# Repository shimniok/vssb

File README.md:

A Vehicle Speed Sensor Buffer (VSSB) for GM Throttle Body Injection (TBI) ECM on my 86 Jeep
Grand Wagoneer.

The Jeep GW uses a VSS for cruise control that outputs 8-pulse (8000 pulses/mile) sine wave
This circuit and firmware convert the OEM VSS signal to a 2-pulse square wave 5V signal
compatible with the GM TBI ECM ('7747) that I'm using.

It also outputs a 4-pulse signal which would be used (I think) by electronic GM speedos. 
The GW speedo, of course, is mechanical.

So what's the advantage of having a working speed sensor? At least a couple of TBI features
are enabled. The ECM is able to distinguish between idle mode (vehicle speed < 4mph) and
throttle-off coasting.  Additionally, Deceleration Fuel Cut-Off (DCFO) mode is enabled in
part based on speed.  And, if enabled, lean highway cruise is based on speed as well.

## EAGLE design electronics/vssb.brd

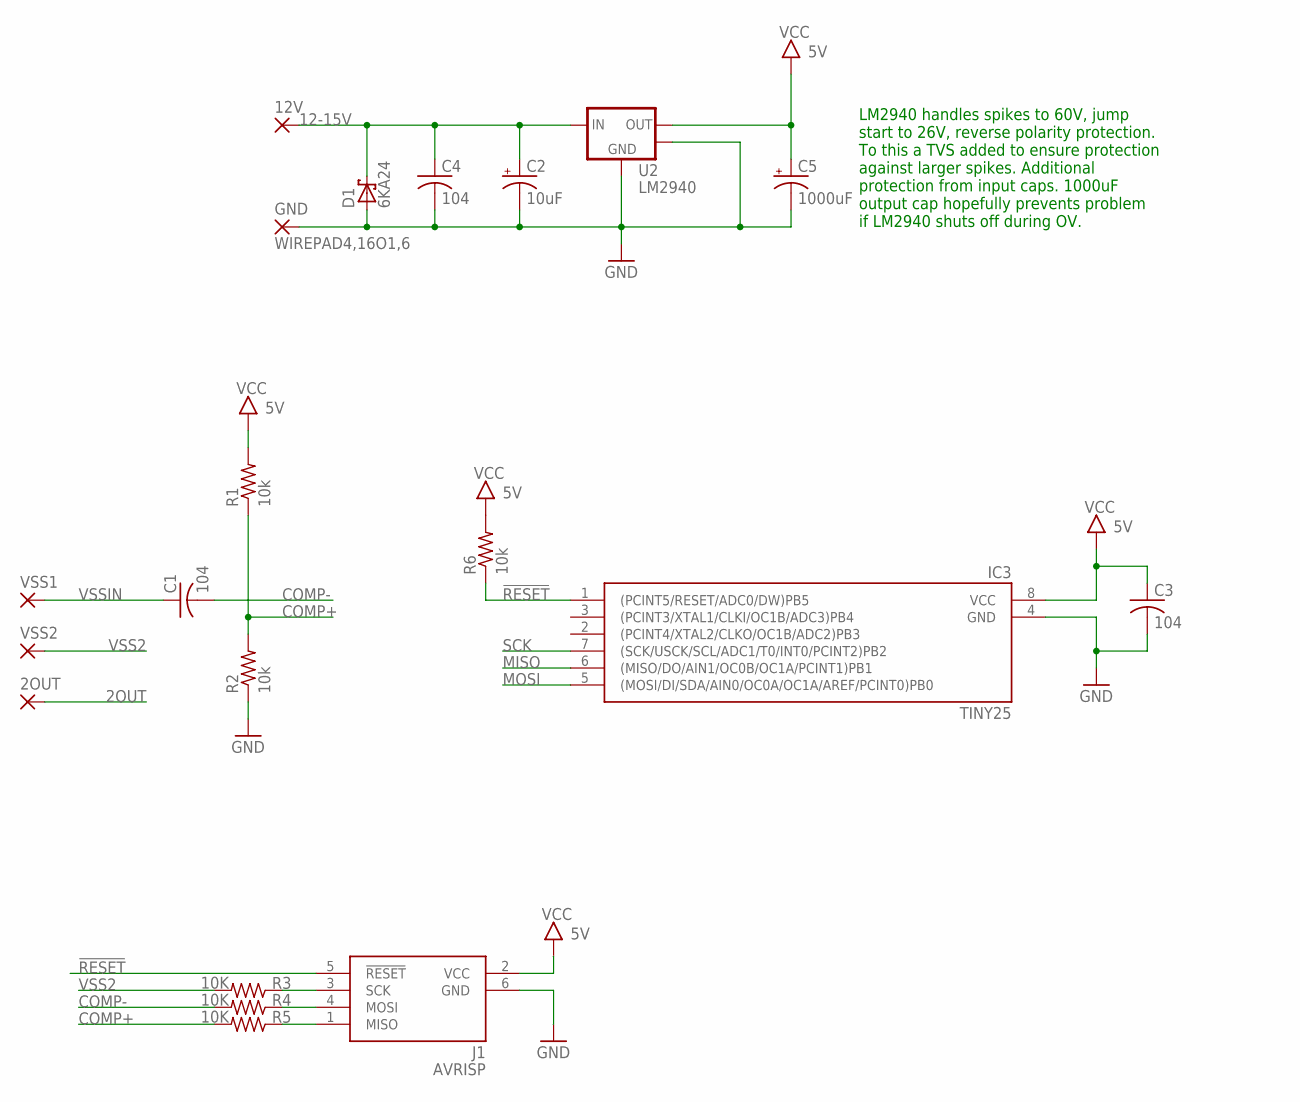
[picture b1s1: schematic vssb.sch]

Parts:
2OUT, 12V: WIREPAD4,16O1,6; 4,16O1,6
C1: 104; C050-024X044
C2: 10uF; E2,5-6
C3, C4: 104; C0603
C5: 1000uF; E5-13
D1: 6KA24; P600
GND: WIREPAD4,16O1,6; 4,16O1,6
IC3: TINY25; SOIC8N
J1: AVRISP; CON6P2R
R1, R2, R6: 10k; R0603
R3, R4, R5: 10K; R0603
U2: LM2940; SOT-223-3
VSS1, VSS2: WIREPAD4,16O1,6; 4,16O1,6

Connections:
2OUT: 2OUT.1
12-15V: 12V.1, C2.+, C4.1, D1.C, U2.1 (VIN)
!RESET: IC3.1 ((PCINT5/RESET/ADC0/DW)PB5), J1.5 (!RESET), R6.1
COMP+: R1.1, R2.2, R5.2
COMP-: C1.2, R4.2
GND: C2.-, C3.2, C4.2, C5.-, D1.A, GND.1, IC3.4 (GND), J1.6 (GND), R2.1, U2.2 (GND), U2.4 (TAB)
MISO: IC3.6 ((MISO/DO/AIN1/OC0B/OC1A/PCINT1)PB1), J1.1 (MISO), R5.1
MOSI: IC3.5 ((MOSI/DI/SDA/AIN0/OC0A/OC1A/AREF/PCINT0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), J1.4 (MOSI), R4.1
SCK: IC3.7 ((SCK/USCK/SCL/ADC1/T0/INT0/PCINT2)PB2), J1.3 (SCK), R3.1
VCC: C3.1, C5.+, IC3.8 (VCC), J1.2 (VCC), R1.2, R6.2, U2.3 (VOUT)
VSS2: R3.2, VSS2.1
VSSIN: C1.1, VSS1.1

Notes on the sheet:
LM2940 handles spikes to 60V, jump start to 26V, reverse polarity protection. To this a TVS added to ensure protection against larger spikes. Additional protection from input caps. 1000uF output cap hopefully prevents problem if LM2940 shuts off during OV.

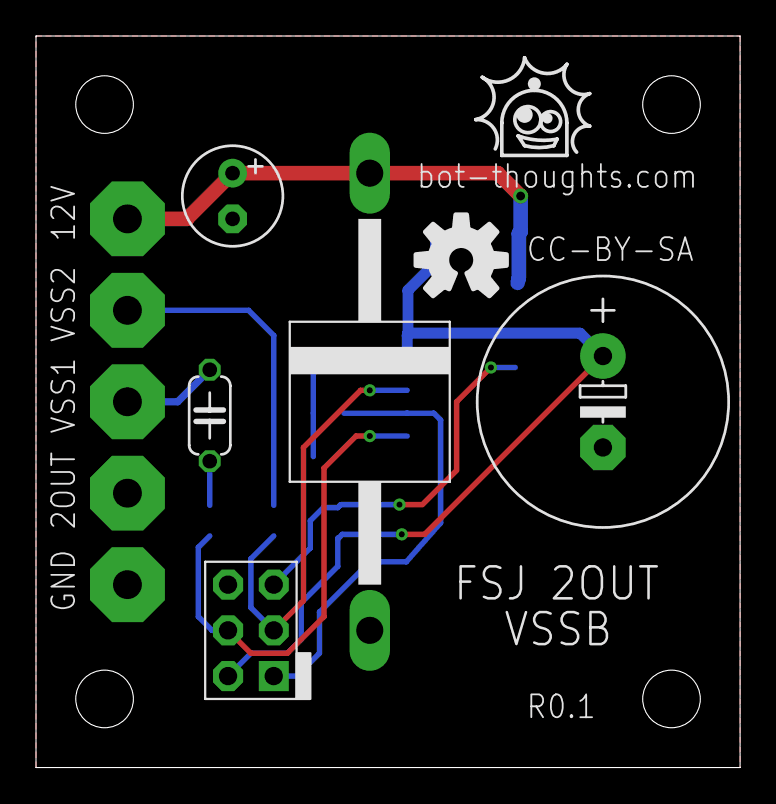
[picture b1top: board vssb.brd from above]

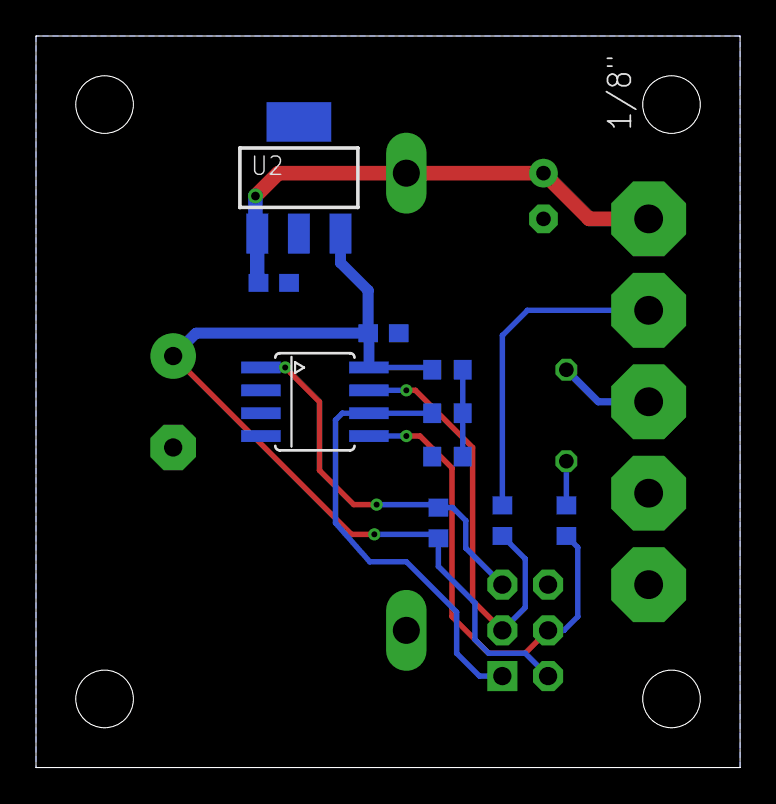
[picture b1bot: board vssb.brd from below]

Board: 2 copper layers, 39.1 x 40.6 mm, 20 parts (10 on the bottom side), 11 nets.

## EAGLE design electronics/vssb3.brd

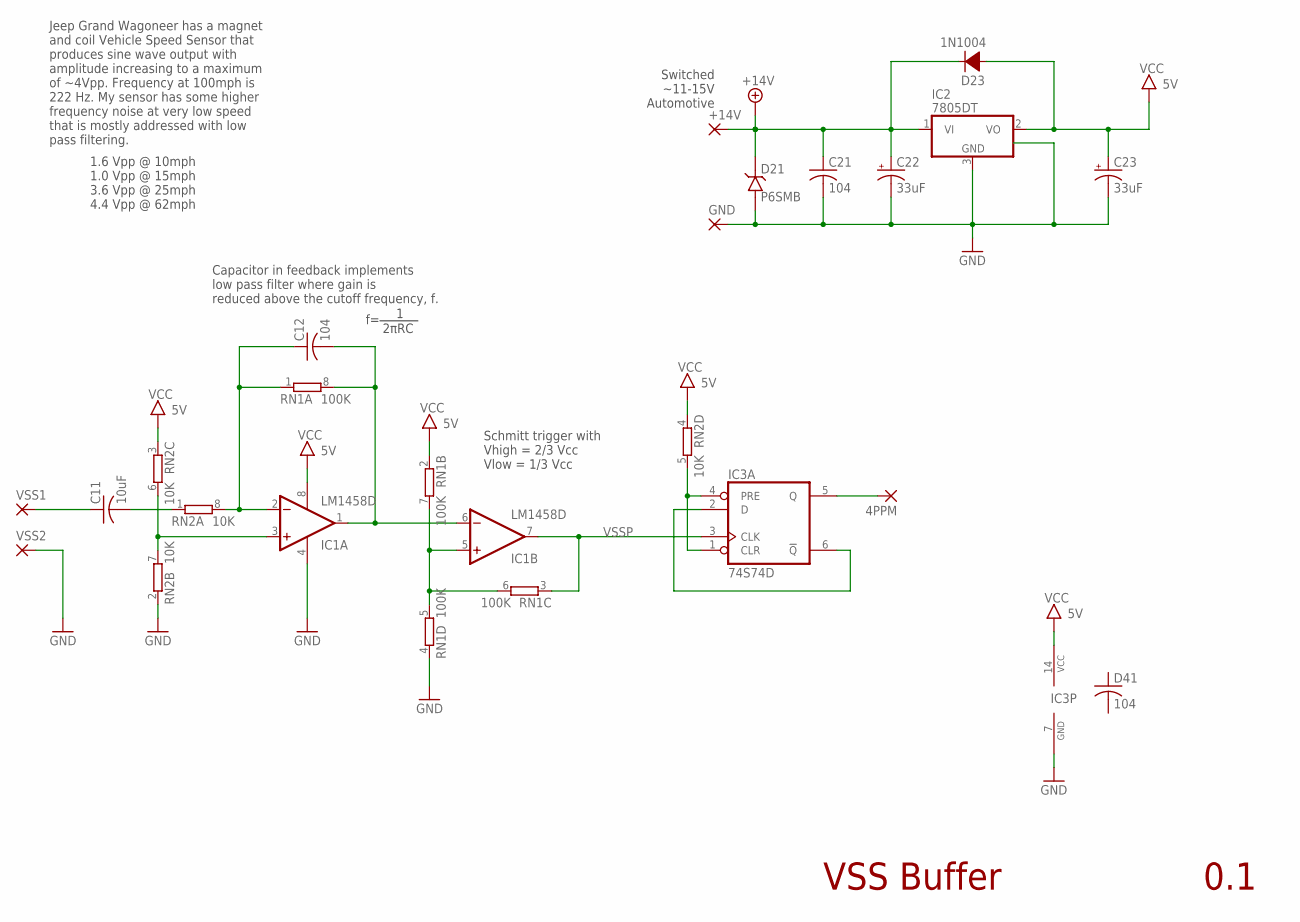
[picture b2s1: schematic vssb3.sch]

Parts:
4PPM: WIREPAD3,17/1,3; 3,17/1,3
+14V: WIREPAD3,17/1,3; 3,17/1,3
C11: 10uF; C1206
C12, C21: 104; C0603
C22, C23: 33uF; SMC_B
D21: P6SMB; DO-214AA
D23: 1N1004; SMA
D41: 104; C0603
GND: WIREPAD3,17/1,3; 3,17/1,3
IC1: LM1458D; SO08
IC2: 7805DT; TO252
IC3: 74S74D; SO14
RN1: 100K; EXB38V
RN2: 10K; EXB38V
VSS1, VSS2: WIREPAD3,17/1,3; 3,17/1,3

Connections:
4PPM: 4PPM.1, IC3.5 (Q)
+14V: +14V.1, C21.1, C22.+, D21.P$1 (C), D23.C, IC2.1 (VI)
GND: C21.2, C22.-, C23.-, D21.P$2 (A), GND.1, IC1.4 (V-), IC2.3 (GND), IC3.7 (GND), RN1.4 (1), RN2.2 (1), VSS2.1
unnamed: C11.2, RN2.1
unnamed: C12.1, IC1.2 (-IN), RN1.1, RN2.8 (2)
unnamed: IC1.3 (+IN), RN2.6 (2), RN2.7 (2)
unnamed: IC1.5 (+IN), RN1.5 (2), RN1.6 (2), RN1.7 (2)
unnamed: IC3.2 (D), IC3.6 (!Q)
unnamed: IC3.1 (CLR), IC3.4 (PRE), RN2.5 (2)
OUT1: C12.2, IC1.1 (OUT), IC1.6 (-IN), RN1.8 (2)
VCC: C23.+, D23.A, IC1.8 (V+), IC2.2 (VO), IC3.14 (VCC), RN1.2 (1), RN2.3 (1), RN2.4 (1)
VSS1: C11.1, VSS1.1
VSSP: IC1.7 (OUT), IC3.3 (CLK), RN1.3 (1)

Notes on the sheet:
Switched ~11-15V Automotive
Jeep Grand Wagoneer has a magnet and coil Vehicle Speed Sensor that produces sine wave output with amplitude increasing to a maximum of ~4Vpp. Frequency at 100mph is 222 Hz. My sensor has some higher frequency noise at very low speed that is mostly addressed with low pass filtering.
1.6 Vpp @ 10mph 1.0 Vpp @ 15mph 3.6 Vpp @ 25mph 4.4 Vpp @ 62mph
Capacitor in feedback implements low pass filter where gain is reduced above the cutoff frequency, f.
Schmitt trigger with Vhigh = 2/3 Vcc Vlow = 1/3 Vcc
2πRC
VSS Buffer
0.1

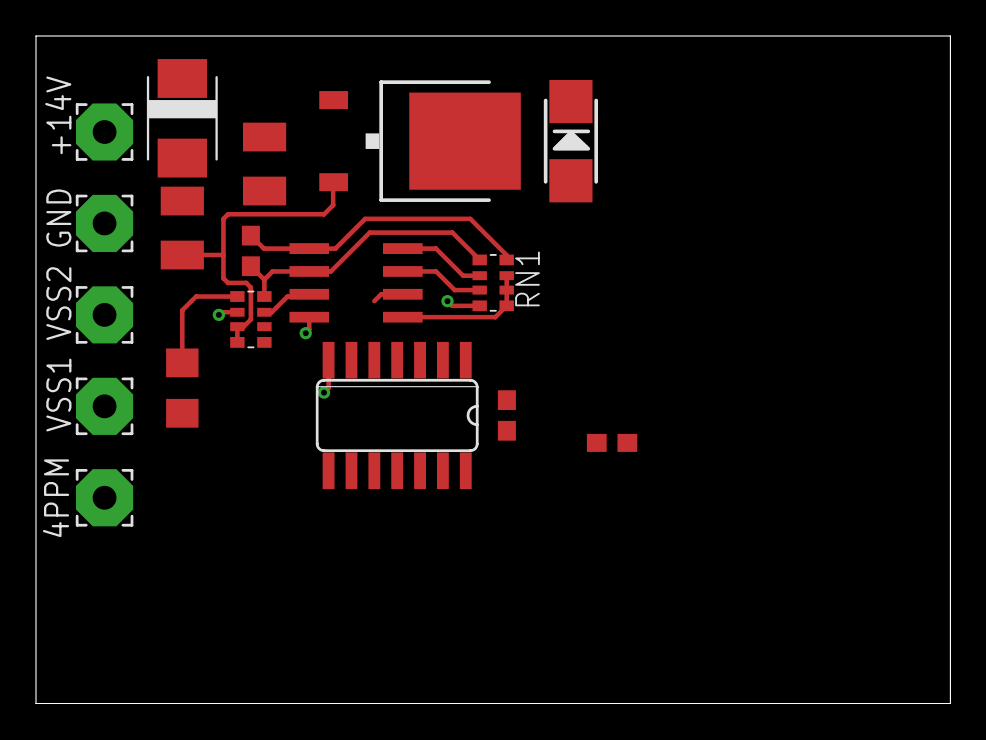
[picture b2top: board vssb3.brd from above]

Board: 2 copper layers, 50.8 x 37.1 mm, 18 parts (0 on the bottom side), 13 nets.

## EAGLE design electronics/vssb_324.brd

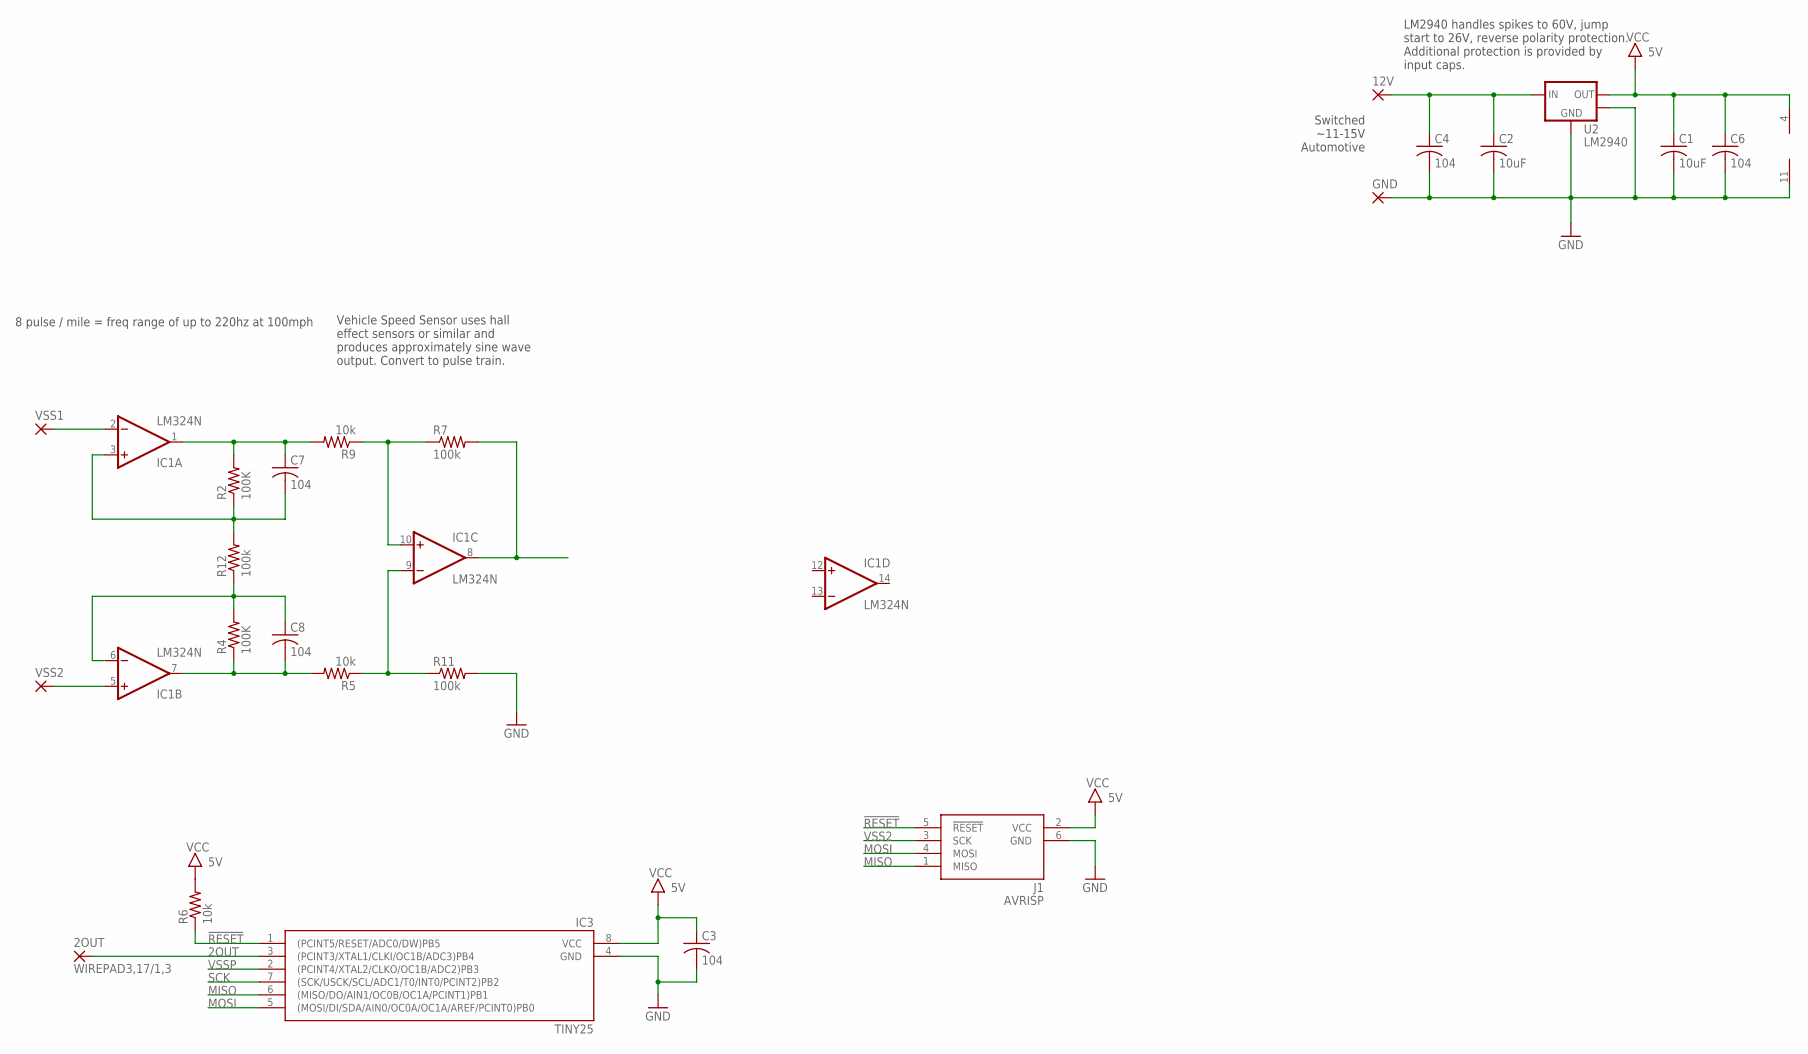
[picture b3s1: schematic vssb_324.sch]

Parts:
2OUT, 12V: WIREPAD3,17/1,3; 3,17/1,3
C1, C2: 10uF; C1206
C3, C4, C6, C7, C8: 104; C0603
GND: WIREPAD3,17/1,3; 3,17/1,3
IC1: LM324N; DIL14
IC3: TINY25; DIL08
J1: AVRISP; CON6P2R
R2, R4: 100K; R0603
R5, R6, R9: 10k; R0603
R7, R11, R12: 100k; R0603
U2: LM2940; TO263-3
VSS1, VSS2: WIREPAD3,17/1,3; 3,17/1,3

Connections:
2OUT: 2OUT.1, IC3.3 ((PCINT3/XTAL1/CLKI/OC1B/ADC3)PB4)
12-15V: 12V.1, C2.1, C4.1, U2.1 (VIN)
!RESET: IC3.1 ((PCINT5/RESET/ADC0/DW)PB5), J1.5 (!RESET), R6.1
GND: C1.2, C2.2, C3.2, C4.2, C6.2, GND.1, IC1.11 (V-), IC3.4 (GND), J1.6 (GND), R11.2, U2.2 (GND), U2.4 (TAB)
MISO: IC3.6 ((MISO/DO/AIN1/OC0B/OC1A/PCINT1)PB1), J1.1 (MISO)
MOSI: IC3.5 ((MOSI/DI/SDA/AIN0/OC0A/OC1A/AREF/PCINT0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), J1.4 (MOSI)
unnamed: C8.1, IC1.6 (-IN), R4.2, R12.1
unnamed: C7.2, IC1.3 (+IN), R2.1, R12.2
unnamed: IC1.8 (OUT), R7.2
unnamed: C7.1, IC1.1 (OUT), R2.2, R9.2
unnamed: C8.2, IC1.7 (OUT), R4.1, R5.2
unnamed: IC1.10 (+IN), R7.1, R9.1
unnamed: IC1.9 (-IN), R5.1, R11.1
SCK: IC3.7 ((SCK/USCK/SCL/ADC1/T0/INT0/PCINT2)PB2)
VCC: C1.1, C3.1, C6.1, IC1.4 (V+), IC3.8 (VCC), J1.2 (VCC), R6.2, U2.3 (VOUT)
VSS1: IC1.2 (-IN), VSS1.1
VSS2: IC1.5 (+IN), J1.3 (SCK), VSS2.1
VSSP: IC3.2 ((PCINT4/XTAL2/CLKO/OC1B/ADC2)PB3)

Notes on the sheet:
LM2940 handles spikes to 60V, jump start to 26V, reverse polarity protection. Additional protection is provided by input caps.
Switched ~11-15V Automotive
Vehicle Speed Sensor uses hall effect sensors or similar and produces approximately sine wave output. Convert to pulse train.
8 pulse / mile = freq range of up to 220hz at 100mph

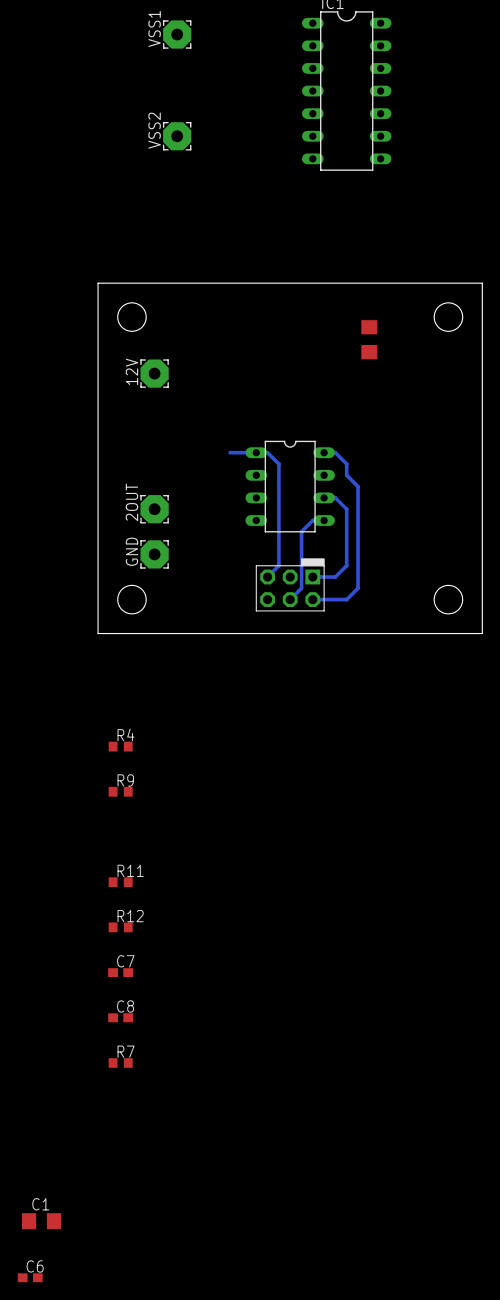
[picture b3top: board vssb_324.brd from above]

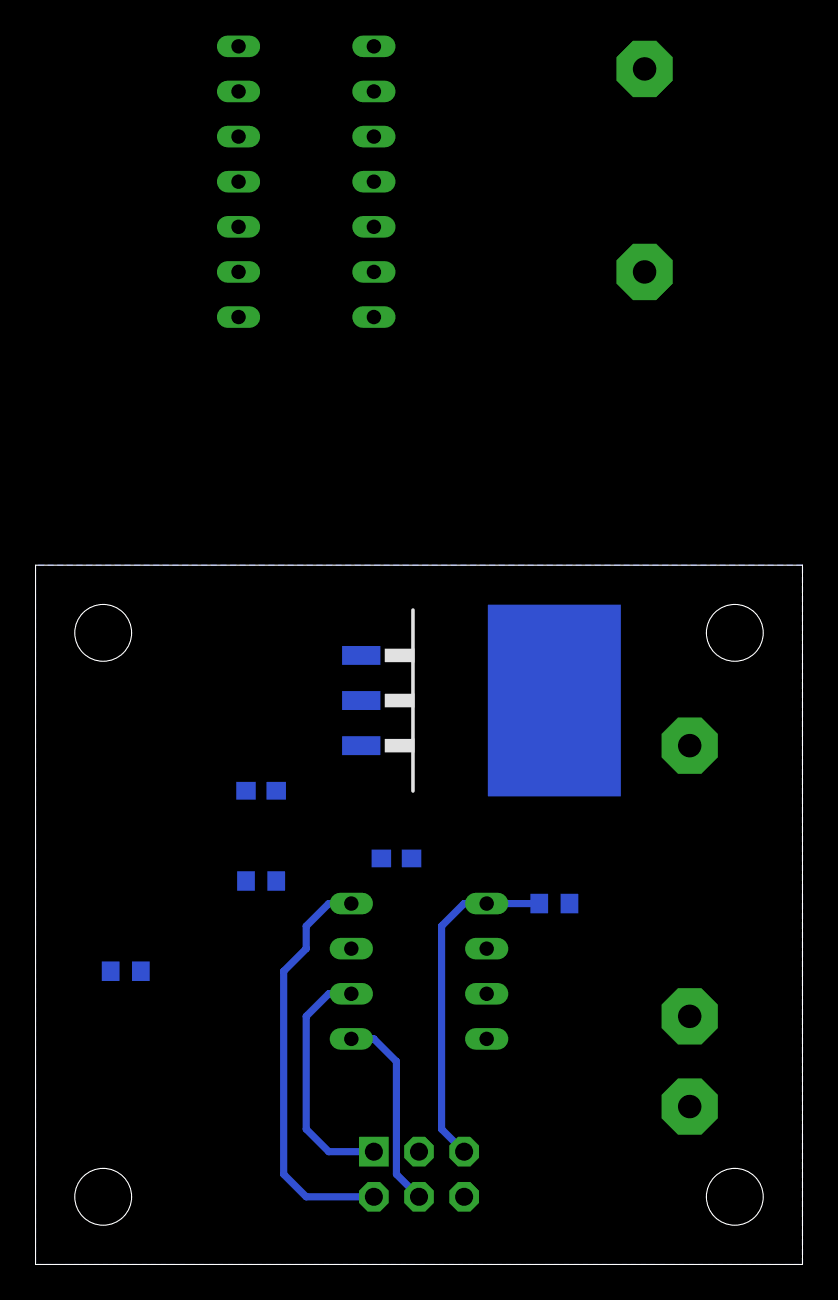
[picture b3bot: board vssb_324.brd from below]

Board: 2 copper layers, 43.2 x 39.4 mm, 24 parts (6 on the bottom side), 16 nets.

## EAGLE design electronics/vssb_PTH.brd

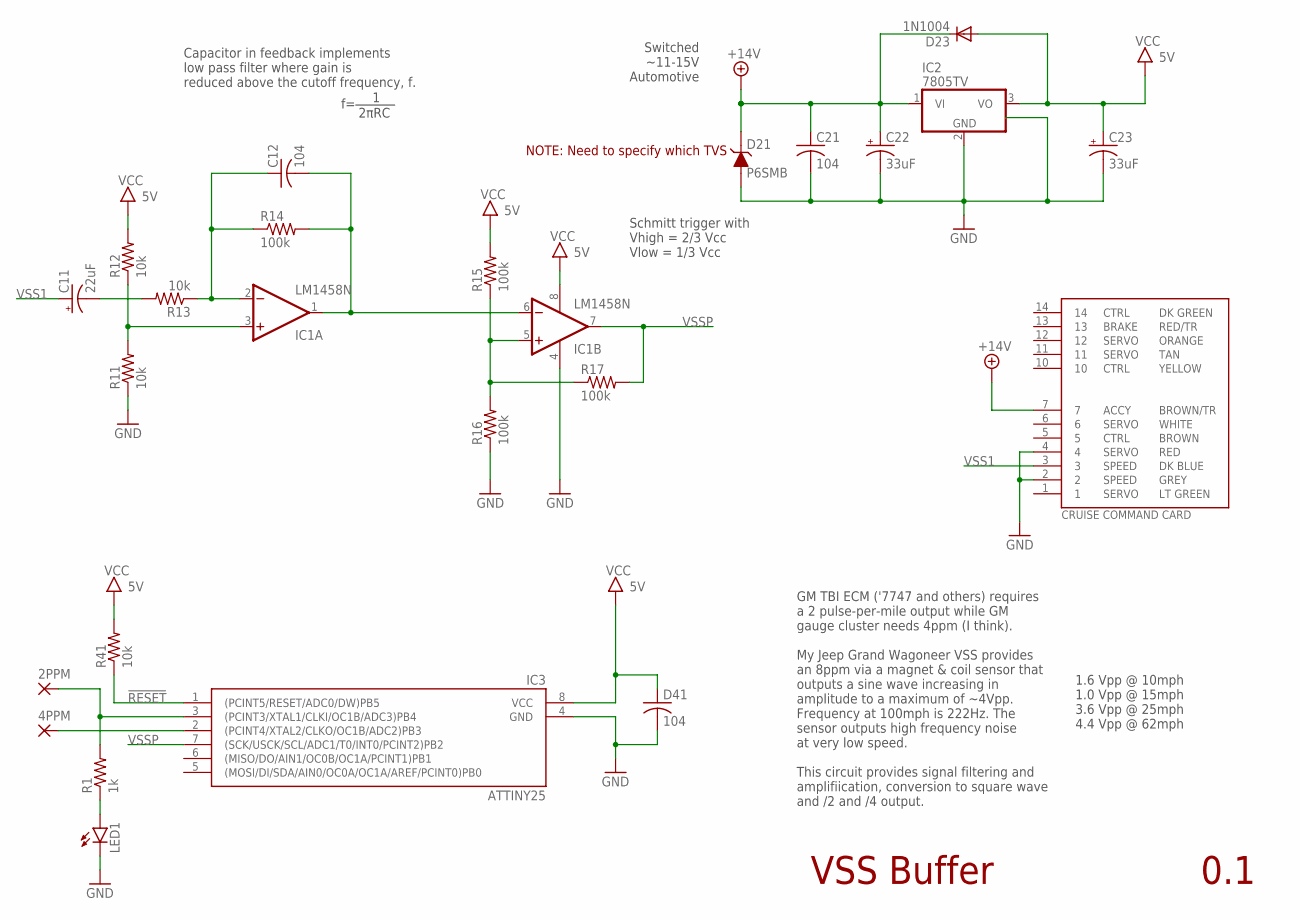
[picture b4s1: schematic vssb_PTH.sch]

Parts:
2PPM, 4PPM: WIREPAD3,17/1,3; 3,17/1,3
C11: 22uF; E5-5
C12, C21: 104; C050-024X044
C22, C23: 33uF; E2,5-6
D21: P6SMB; DO-214AA
D23: 1N1004; DO41-10
D41: 104; C050-024X044
IC1: LM1458N; DIL08
IC2: 7805TV; TO220V
IC3: ATTINY25; DIL08
LED1: LED3MM
R1: 1k; 0204/5
R11, R12, R13, R41: 10k; 0204/5
R14, R15, R16, R17: 100k; 0204/5
U$4: FSJ_CC_CARD; FSJ_CC

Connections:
!RESET: IC3.1 ((PCINT5/RESET/ADC0/DW)PB5), R41.1
+14V: C21.1, C22.+, D21.P$1 (C), D23.C, IC2.1 (VI), U$4.7
/2: 2PPM.1, IC3.3 ((PCINT3/XTAL1/CLKI/OC1B/ADC3)PB4), R1.2
GND: C21.2, C22.-, C23.-, D21.P$2 (A), D41.2, IC1.4 (V-), IC2.2 (GND), IC3.4 (GND), LED1.K (C), R11.1, R16.1, U$4.2, U$4.4
unnamed: C11.-, R13.2
unnamed: C12.1, IC1.2 (-IN), R13.1, R14.1
unnamed: IC1.3 (+IN), R11.2, R12.1
unnamed: IC1.5 (+IN), R15.1, R16.2, R17.1
unnamed: LED1.A, R1.1
unnamed: 4PPM.1, IC3.2 ((PCINT4/XTAL2/CLKO/OC1B/ADC2)PB3)
OUT1: C12.2, IC1.1 (OUT), IC1.6 (-IN), R14.2
VCC: C23.+, D23.A, D41.1, IC1.8 (V+), IC2.3 (VO), IC3.8 (VCC), R12.2, R15.2, R41.2
VSS1: C11.+, U$4.3
VSSP: IC1.7 (OUT), IC3.7 ((SCK/USCK/SCL/ADC1/T0/INT0/PCINT2)PB2), R17.2

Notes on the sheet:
Switched ~11-15V Automotive
1.6 Vpp @ 10mph 1.0 Vpp @ 15mph 3.6 Vpp @ 25mph 4.4 Vpp @ 62mph
Capacitor in feedback implements low pass filter where gain is reduced above the cutoff frequency, f.
Schmitt trigger with Vhigh = 2/3 Vcc Vlow = 1/3 Vcc
2πRC
VSS Buffer
0.1
GM TBI ECM ('7747 and others) requires a 2 pulse-per-mile output while GM gauge cluster needs 4ppm (I think). My Jeep Grand Wagoneer VSS provides an 8ppm via a magnet & coil sensor that outputs a sine wave increasing in amplitude to a maximum of ~4Vpp. Frequency at 100mph is 222Hz. The sensor outpu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
NOTE: Need to specify which TVS

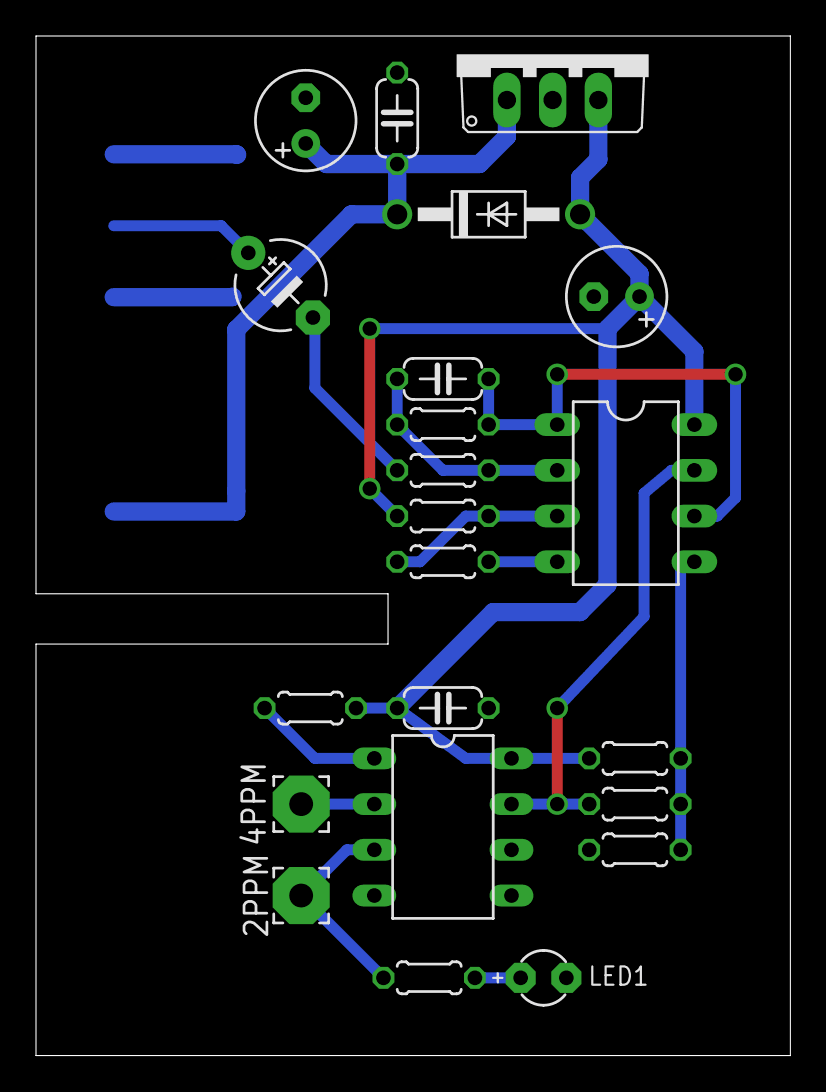
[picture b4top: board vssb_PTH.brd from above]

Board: 2 copper layers, 41.9 x 56.6 mm, 24 parts (1 on the bottom side), 14 nets.

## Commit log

2016-10-07 initial release
2016-10-07 added readme
2016-10-07 gitignore tweak for map files
2016-10-10 minor tweaks to 1458 power, tvs symbol
2016-10-11 ground plane; minor layout moves for some capacitors and regulator, reroute, shrunk board width
2016-10-11 shrunk card edge and board width
2016-12-07 Changed input series cap to 22uF based on experimentation
2016-12-07 configured output ports to start high (to light LEDs); removed commented sleep statements in main while infinite loop
2021-02-10 added additional versions of board/schematic

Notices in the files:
electronics/vssb.brd:
CC-BY-SA
